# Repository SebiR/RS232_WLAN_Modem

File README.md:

# RS232 WLAN Modem
An ESP8266 based device to emulate an old serial modem to get old hardware connected to the internet

## Features
* USB-C power
* Can be used with male and female DSUB connectors
* Small form factor

## Uses
The board was intended to be used as a RS232 modem replacement for an old PC. But with the right firmware it can of course be used for other stuff:
* Wireless RS232 bridge
* IoT/Tasmota/MQT bridge for RS232 defices
* ...

# 3D printed case
There's also a case for 3D printing available!

# Firmware and acknowledgement
The whole device is based on the RS232 Serial WIFI Modem from The Old Net.
The firmware can be found here: https://github.com/ssshake/vintage-computer-wifi-modem

I just wanted to create a more compact version of the hardware.

# Notes
The PCB has plated slots for the USB-C connector. The outline layer in the gerber files has a note for this. You might want to have an eye on the production files if you order the PCBs.

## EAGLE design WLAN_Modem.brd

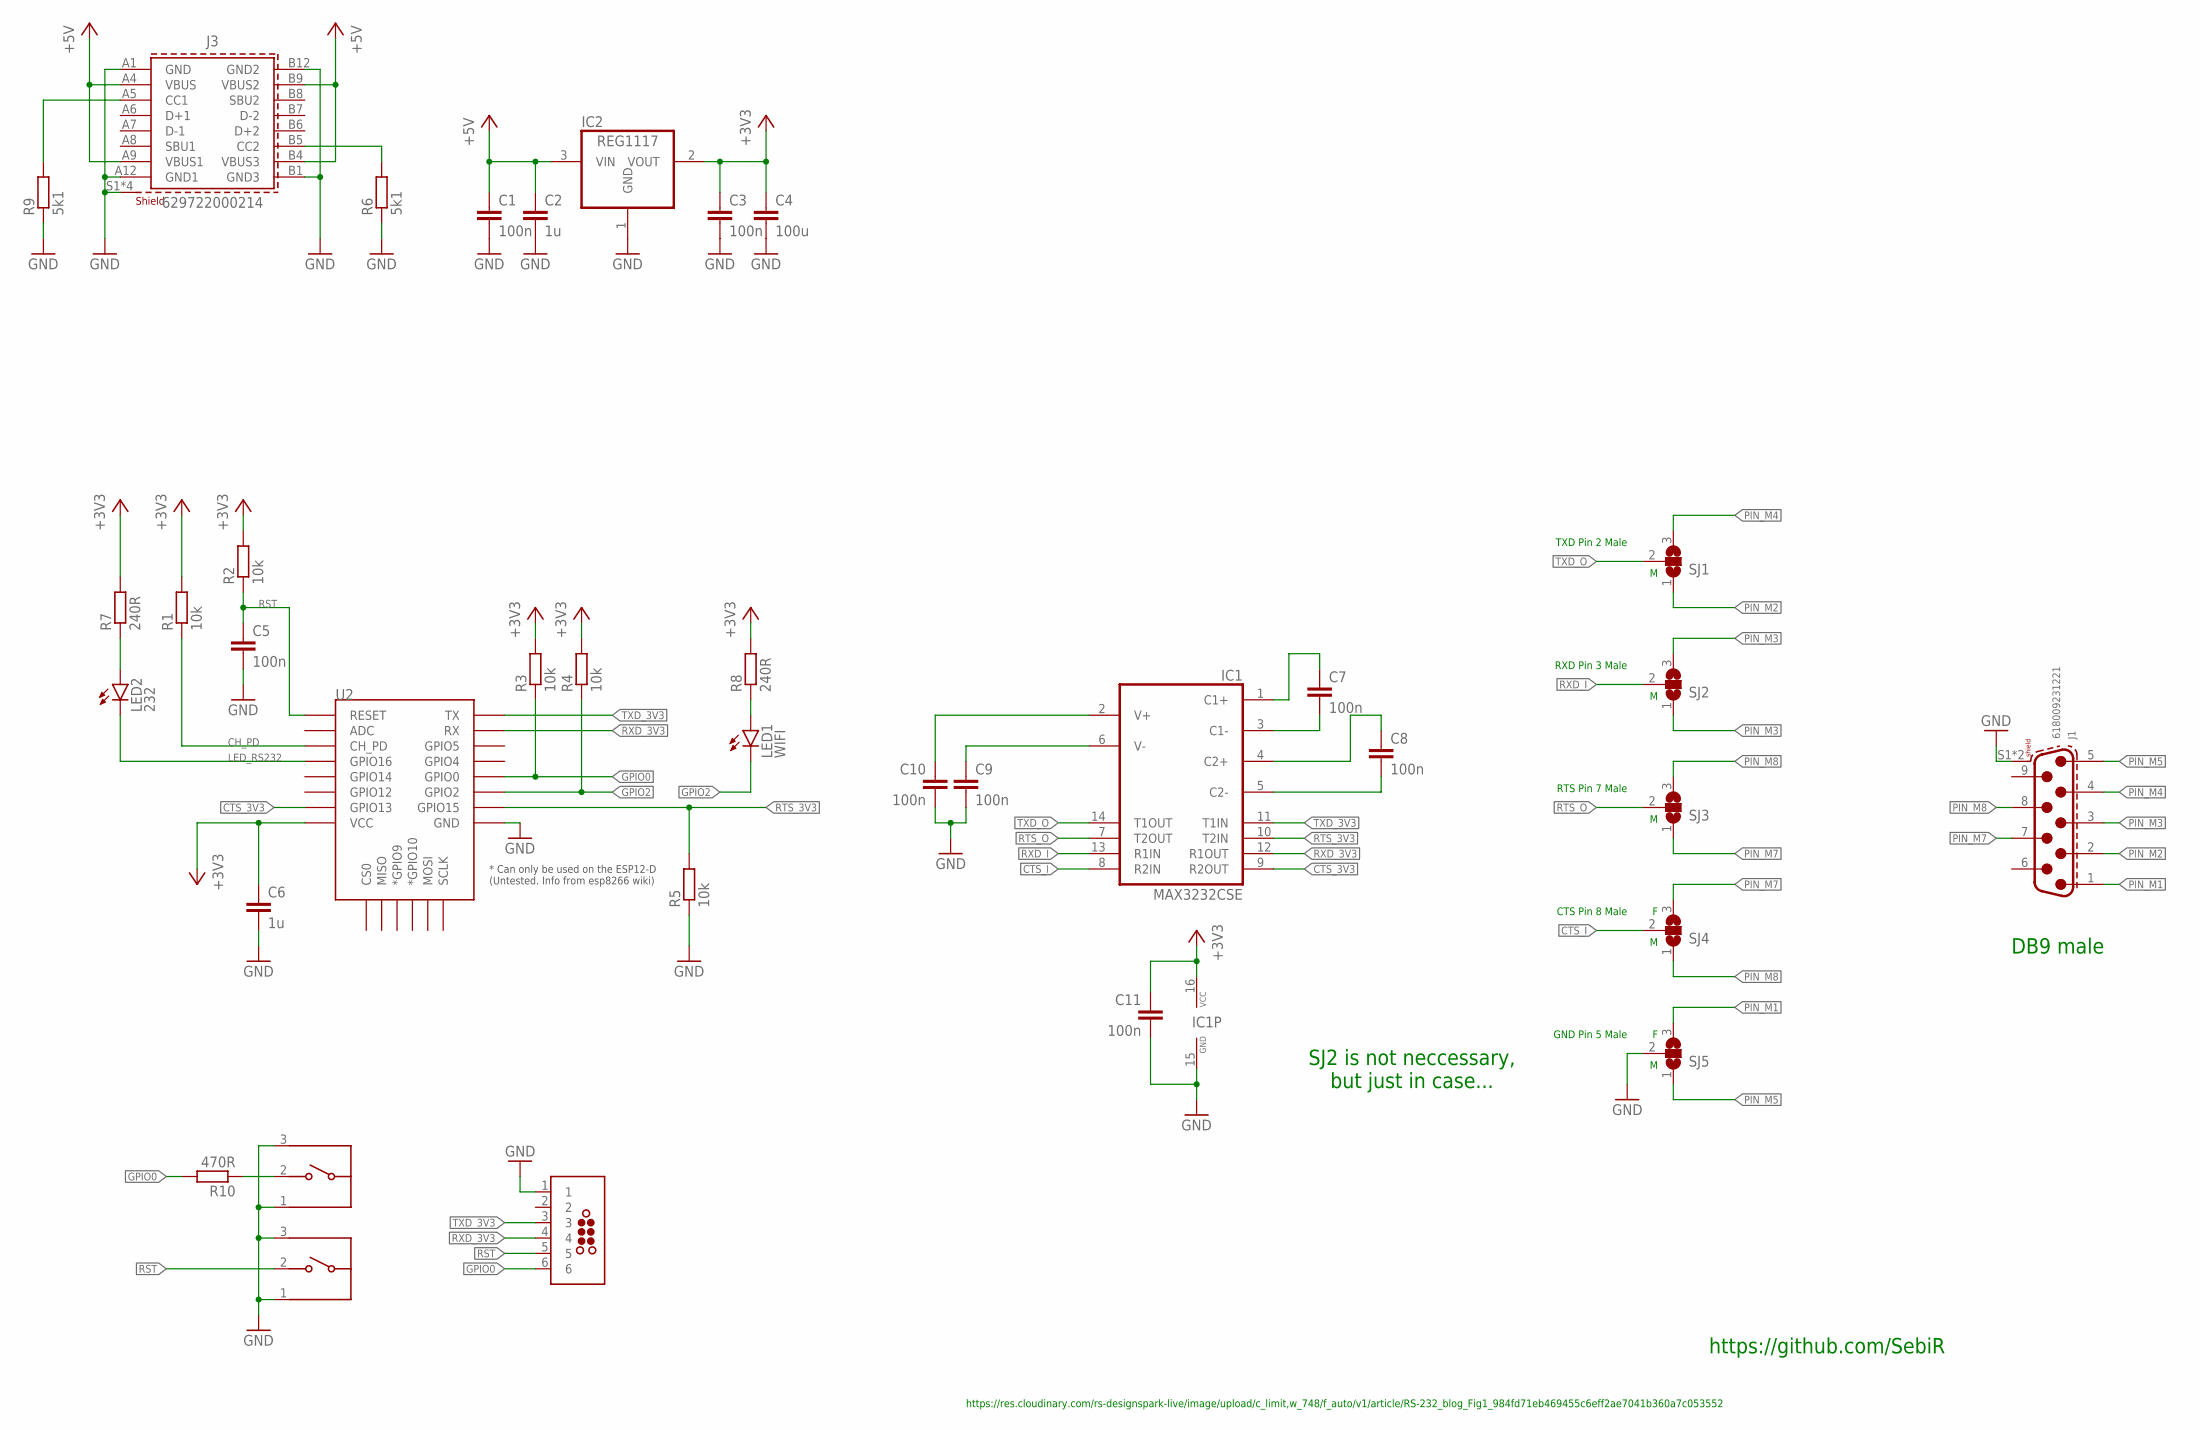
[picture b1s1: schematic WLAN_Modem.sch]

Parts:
C1, C3, C5, C7, C8, C9, C10, C11: 100n; C0603
C2, C6: 1u; C0603
C4: 100u; C0603
IC1: MAX3232CSE; SO16
IC2: REG1117; SOT223
J1: 618009231221
J3: 629722000214
J4: TAG-CONNECT_TC2030-MCP-NL
LED1: WIFI; CHIP-LED0603
LED2: 232; CHIP-LED0603
R1, R2, R3, R4, R5: 10k; R0603
R6, R9: 5k1; R0603
R7, R8: 240R; R0603
R10: 470R; R0603
S1, S2: 436333033816
SJ1, SJ2, SJ3, SJ4, SJ5: SJ2W; SJ_2
U2: ESP12ESMD; ESP12E-SMD

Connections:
2: J4.2
+3V3: C3.1, C4.1, C6.1, C11.1, IC1.16 (VCC), IC2.2 (VOUT), R1.2, R2.2, R3.2, R4.2, R7.2, R8.2, U2.VCC
+5V: C1.1, C2.1, IC2.3 (VIN), J3.A4 (VBUS), J3.A9 (VBUS1), J3.B4 (VBUS3), J3.B9 (VBUS2)
CH_PD: R1.1, U2.CH_PD
CTS_3V3: IC1.9 (R2OUT), U2.GPIO13
CTS_I: IC1.8 (R2IN), SJ4.2
GND: C1.2, C2.2, C3.2, C4.2, C5.2, C6.2, C9.2, C10.2, C11.2, IC1.15 (GND), IC2.1 (GND), J1.S1 (SHIELD), J1.S2 (SHIELD), J3.A1 (GND), J3.A12 (GND1), J3.B1 (GND3), J3.B12 (GND2), J3.S1 (SHIELD), J3.S2 (SHIELD), J3.S3 (SHIELD), J3.S4 (SHIELD), J4.1, R5.1, R6.1, R9.1, S1.1, S1.3, S2.1, S2.3, SJ5.2, U2.GND
GPIO0: J4.6, R3.1, R10.2, U2.GPIO0
GPIO2: LED1.C, R4.1, U2.GPIO2
LED_RS232: LED2.C, U2.GPIO16
unnamed: LED1.A, R8.1
unnamed: J3.A5 (CC1), R9.2
unnamed: LED2.A, R7.1
unnamed: J3.B5 (CC2), R6.2
unnamed: R10.1, S2.2
unnamed: C7.2, IC1.3 (C1-)
unnamed: C7.1, IC1.1 (C1+)
unnamed: C8.1, IC1.4 (C2+)
unnamed: C8.2, IC1.5 (C2-)
unnamed: C10.1, IC1.2 (V+)
unnamed: C9.1, IC1.6 (V-)
PIN_M1: J1.1, SJ5.3
PIN_M2: J1.2, SJ1.1
PIN_M3: J1.3, SJ2.1, SJ2.3
PIN_M4: J1.4, SJ1.3
PIN_M5: J1.5, SJ5.1
PIN_M7: J1.7, SJ3.1, SJ4.3
PIN_M8: J1.8, SJ3.3, SJ4.1
RST: C5.1, J4.5, R2.1, S1.2, U2.RESET
RTS_3V3: IC1.10 (T2IN), R5.2, U2.GPIO15
RTS_O: IC1.7 (T2OUT), SJ3.2
RXD_3V3: IC1.12 (R1OUT), J4.4, U2.RXD0 (RX)
RXD_I: IC1.13 (R1IN), SJ2.2
TXD_3V3: IC1.11 (T1IN), J4.3, U2.TXD0 (TX)
TXD_O: IC1.14 (T1OUT), SJ1.2

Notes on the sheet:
GND Pin 5 Male
CTS Pin 8 Male
RTS Pin 7 Male
RXD Pin 3 Male
TXD Pin 2 Male
https://res.cloudinary.com/rs-designspark-live/image/upload/c_limit,w_748/f_auto/v1/article/RS-232_blog_Fig1_984fd71eb469455c6eff2ae7041b360a7c053552
SJ2 is not neccessary, but just in case...
DB9 male
https://github.com/SebiR

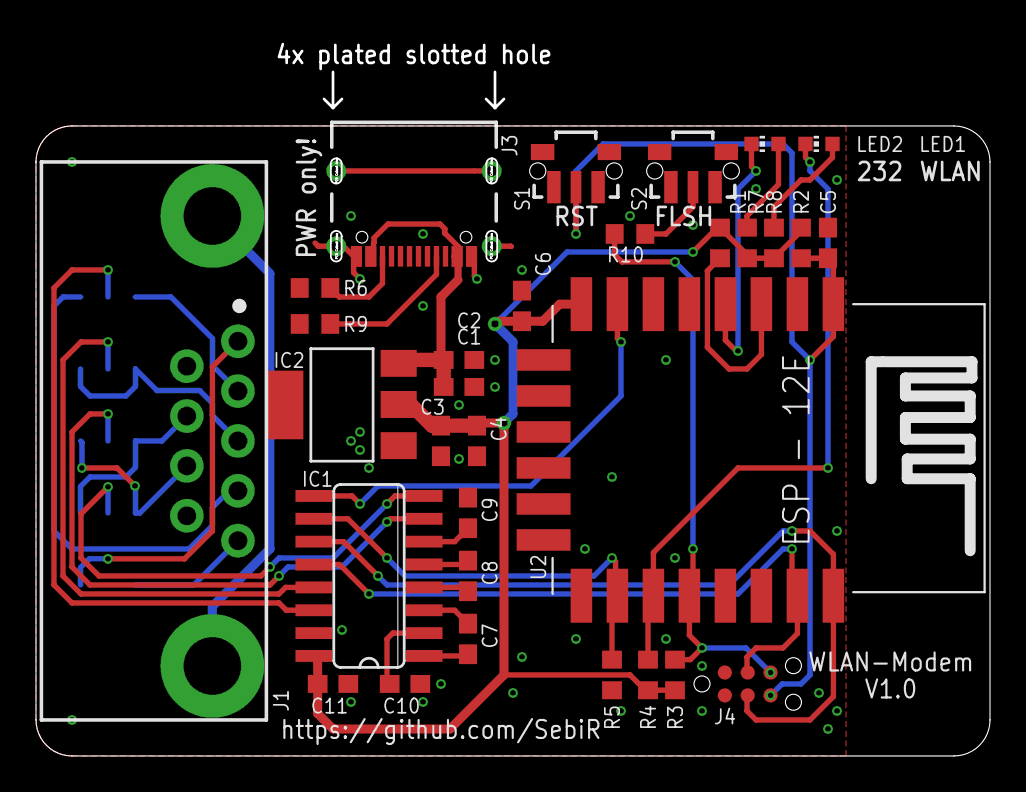
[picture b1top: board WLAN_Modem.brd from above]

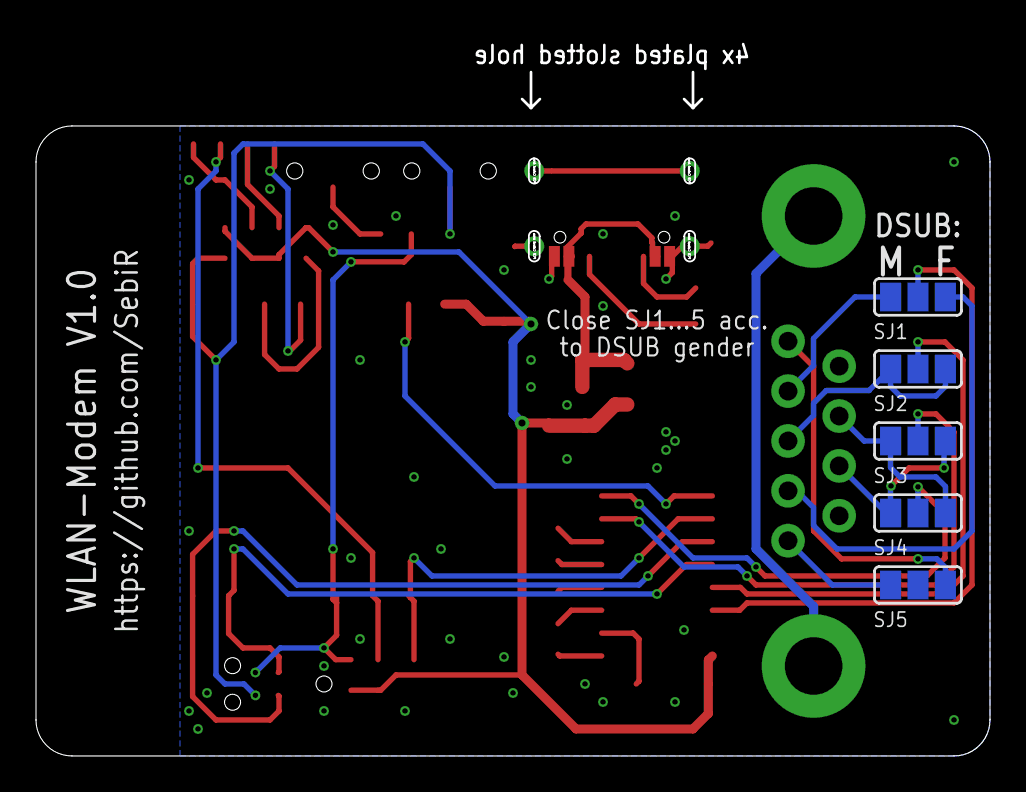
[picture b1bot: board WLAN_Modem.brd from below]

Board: 2 copper layers, 52.8 x 39.8 mm, 36 parts (5 on the bottom side), 34 nets.

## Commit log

2023-12-31 added stl files for the case
2024-01-03 * Optimized layout for manufacturing * Added plated slot note on dimension layer * Updated README.md * Added GERBER files

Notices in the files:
parts and their libraries:
Wurth_Connectors_WR-DSUB: Copyright: Würth Elektronik
Eigene-Rietig: ©2009 ROFA.cz - modified and updated by Robert Darlington ‹rdarlington@gmail.com›
